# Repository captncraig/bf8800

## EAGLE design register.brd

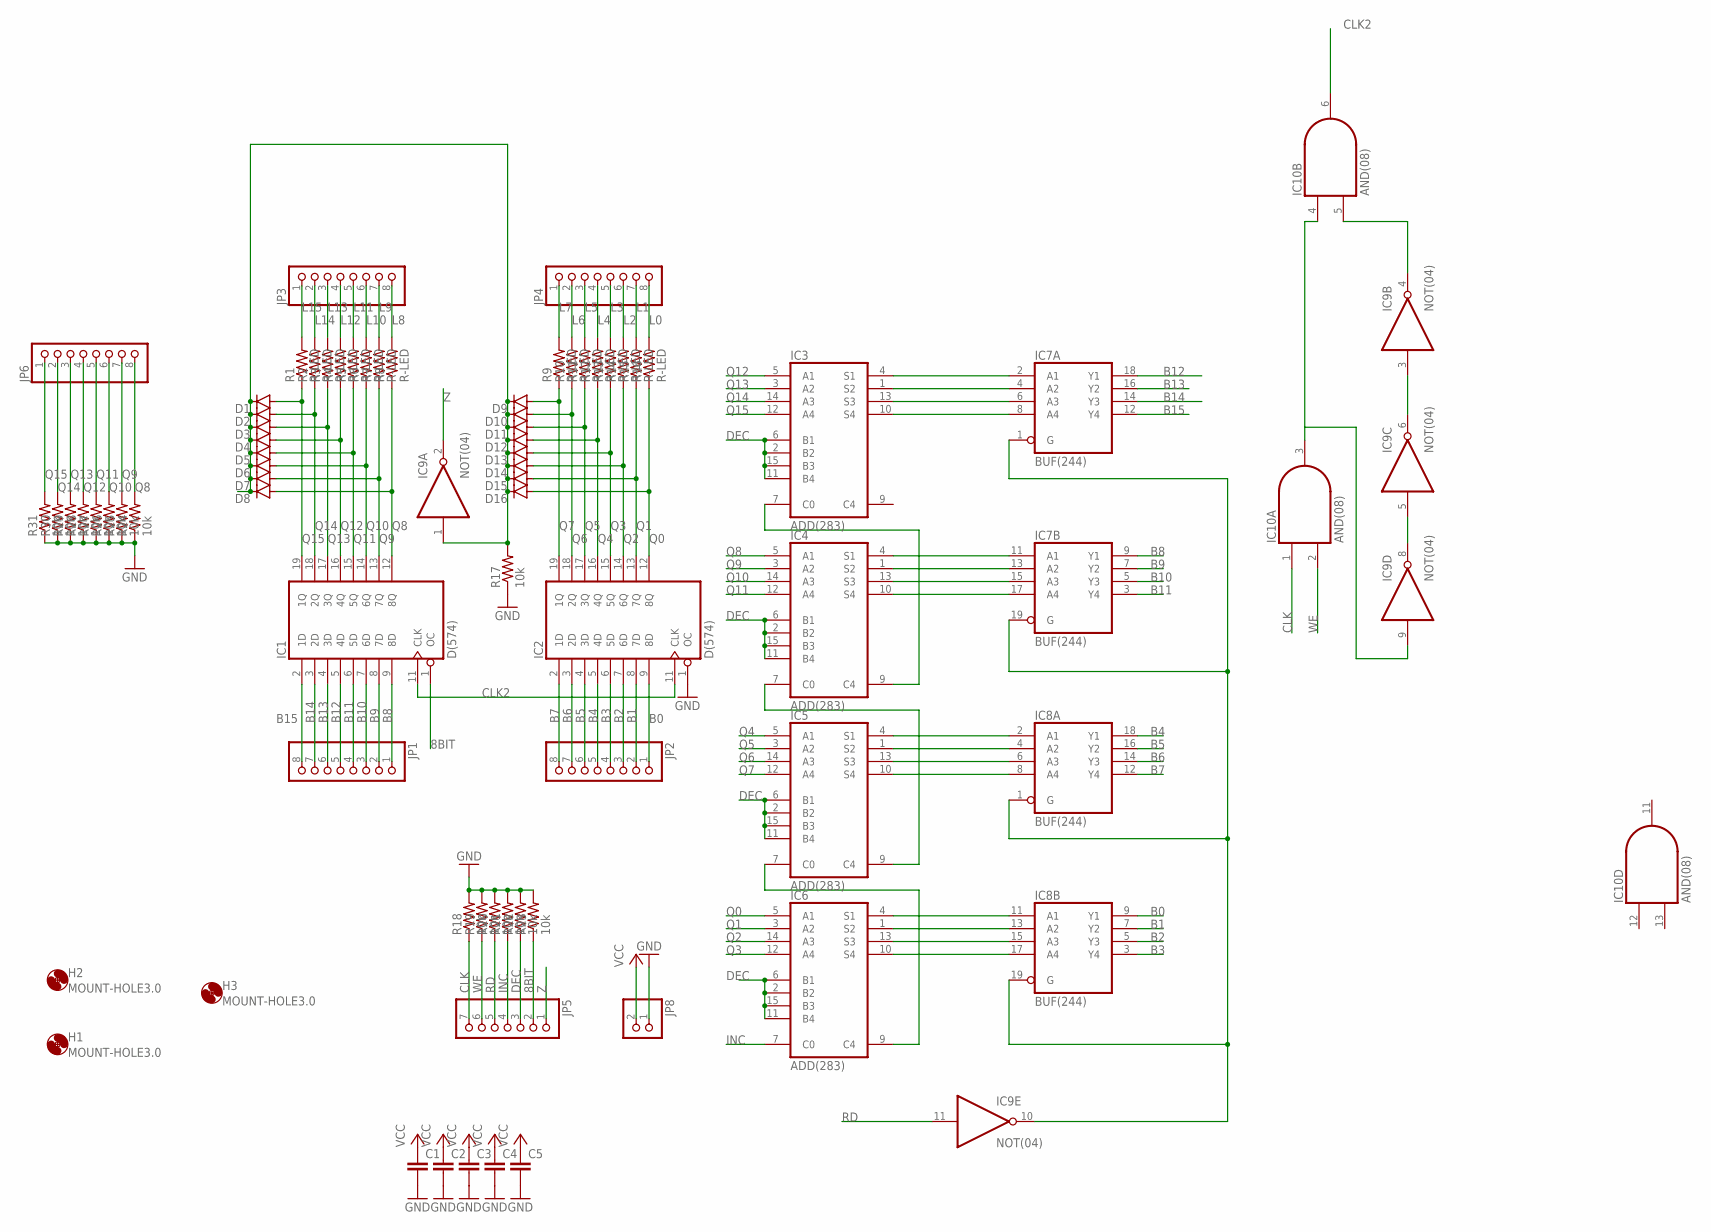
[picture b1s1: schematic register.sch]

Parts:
C1, C2, C3, C4, C5: C-Decouple; C025-025X050
D1, D2, D3, D4, D5, D6, D7, D8, D9, D10, D11, D12, D13, D14, D15, D16: DIODE-D-7.5; D-7.5
H1, H2, H3: MOUNT-HOLE3.0; 3,0
IC1, IC2: D(574); DIL20; MOUSER 595-SN74HCT574NE4
IC3, IC4, IC5, IC6: ADD(283); DIL16; MOUSER 595-CD74HCT283E
IC7, IC8: BUF(244); DIL20; MOUSER 595-SN74HCT244NE4
IC9: NOT(04); DIL14; MOUSER 595-SN74HCT04NE4
IC10: AND(08); DIL14; MOUSER 595-SN74HC08AN
JP1, JP2, JP3, JP4, JP6: PINHD-1X8; 1X08
JP5: PINHD-1X7; 1X07
JP8: PINHD-1X2; 1X02
R1, R2, R3, R4, R5, R6, R7, R8, R9, R10, R11, R12, R13, R14, R15, R16: R-LED; 0204/7
R17, R18, R19, R20, R21, R22, R23, R24, R25, R26, R27, R28, R29, R30, R31: 10k; 0204/7; MOUSER 603-MFR-12FRF5210K

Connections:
8BIT: IC1.1 (OC), JP5.2, R23.1
B0: IC2.9 (8D), IC8.9 (Y1), JP2.1
B1: IC2.8 (7D), IC8.7 (Y2), JP2.2
B2: IC2.7 (6D), IC8.5 (Y3), JP2.3
B3: IC2.6 (5D), IC8.3 (Y4), JP2.4
B4: IC2.5 (4D), IC8.18 (Y1), JP2.5
B5: IC2.4 (3D), IC8.16 (Y2), JP2.6
B6: IC2.3 (2D), IC8.14 (Y3), JP2.7
B7: IC2.2 (1D), IC8.12 (Y4), JP2.8
B8: IC1.9 (8D), IC7.9 (Y1), JP1.1
B9: IC1.8 (7D), IC7.7 (Y2), JP1.2
B10: IC1.7 (6D), IC7.5 (Y3), JP1.3
B11: IC1.6 (5D), IC7.3 (Y4), JP1.4
B12: IC1.5 (4D), IC7.18 (Y1), JP1.5
B13: IC1.4 (3D), IC7.16 (Y2), JP1.6
B14: IC1.3 (2D), IC7.14 (Y3), JP1.7
B15: IC1.2 (1D), IC7.12 (Y4), JP1.8
CLK: IC10.1 (I0), JP5.7, R18.1
CLK2: IC1.11 (CLK), IC2.11 (CLK), IC10.6 (O)
DEC: IC3.2 (B2), IC3.6 (B1), IC3.11 (B4), IC3.15 (B3), IC4.2 (B2), IC4.6 (B1), IC4.11 (B4), IC4.15 (B3), IC5.2 (B2), IC5.6 (B1), IC5.11 (B4), IC5.15 (B3), IC6.2 (B2), IC6.6 (B1), IC6.11 (B4), IC6.15 (B3), JP5.3, R22.1
GND: C1.2, C2.2, C3.2, C4.2, C5.2, IC1.10 (GND), IC2.1 (OC), IC2.10 (GND), IC3.8 (GND), IC4.8 (GND), IC5.8 (GND), IC6.8 (GND), IC7.10 (GND), IC8.10 (GND), IC9.7 (GND), IC10.7 (GND), JP8.1, R17.1, R18.2, R19.2, R20.2, R21.2, R22.2, R23.2, R24.1, R25.1, R26.1, R27.1, R28.1, R29.1, R30.1, R31.1
INC: IC6.7 (C0), JP5.4, R21.1
L0: JP4.8, R16.2
L1: JP4.7, R15.2
L2: JP4.6, R14.2
L3: JP4.5, R13.2
L4: JP4.4, R12.2
L5: JP4.3, R11.2
L6: JP4.2, R10.2
L7: JP4.1, R9.2
L8: JP3.8, R8.2
L9: JP3.7, R7.2
L10: JP3.6, R6.2
L11: JP3.5, R5.2
L12: JP3.4, R4.2
L13: JP3.3, R3.2
L14: JP3.2, R2.2
L15: JP3.1, R1.2
unnamed: IC5.7 (C0), IC6.9 (C4)
unnamed: IC9.9 (I), IC10.3 (O), IC10.4 (I0)
unnamed: D1.C, D2.C, D3.C, D4.C, D5.C, D6.C, D7.C, D8.C, D9.C, D10.C, D11.C, D12.C, D13.C, D14.C, D15.C, D16.C, IC9.1 (I), R17.2
unnamed: IC7.1 (G), IC7.19 (G), IC8.1 (G), IC8.19 (G), IC9.10 (O)
unnamed: IC9.4 (O), IC10.5 (I1)
unnamed: IC9.3 (I), IC9.6 (O)
unnamed: IC9.5 (I), IC9.8 (O)
unnamed: IC4.7 (C0), IC5.9 (C4)
unnamed: IC3.7 (C0), IC4.9 (C4)
unnamed: IC3.4 (S1), IC7.2 (A1)
unnamed: IC3.1 (S2), IC7.4 (A2)
unnamed: IC3.13 (S3), IC7.6 (A3)
unnamed: IC3.10 (S4), IC7.8 (A4)
unnamed: IC4.4 (S1), IC7.11 (A1)
unnamed: IC4.1 (S2), IC7.13 (A2)
unnamed: IC4.13 (S3), IC7.15 (A3)
unnamed: IC4.10 (S4), IC7.17 (A4)
unnamed: IC5.4 (S1), IC8.2 (A1)
unnamed: IC5.1 (S2), IC8.4 (A2)
unnamed: IC5.13 (S3), IC8.6 (A3)
unnamed: IC5.10 (S4), IC8.8 (A4)
unnamed: IC6.4 (S1), IC8.11 (A1)
unnamed: IC6.1 (S2), IC8.13 (A2)
unnamed: IC6.13 (S3), IC8.15 (A3)
unnamed: IC6.10 (S4), IC8.17 (A4)
Q0: D16.A, IC2.12 (8Q), IC6.5 (A1), R16.1
Q1: D15.A, IC2.13 (7Q), IC6.3 (A2), R15.1
Q2: D14.A, IC2.14 (6Q), IC6.14 (A3), R14.1
Q3: D13.A, IC2.15 (5Q), IC6.12 (A4), R13.1
Q4: D12.A, IC2.16 (4Q), IC5.5 (A1), R12.1
Q5: D11.A, IC2.17 (3Q), IC5.3 (A2), R11.1
Q6: D10.A, IC2.18 (2Q), IC5.14 (A3), R10.1
Q7: D9.A, IC2.19 (1Q), IC5.12 (A4), R9.1
Q8: D8.A, IC1.12 (8Q), IC4.5 (A1), JP6.8, R8.1, R24.2
Q9: D7.A, IC1.13 (7Q), IC4.3 (A2), JP6.7, R7.1, R25.2
Q10: D6.A, IC1.14 (6Q), IC4.14 (A3), JP6.6, R6.1, R26.2
Q11: D5.A, IC1.15 (5Q), IC4.12 (A4), JP6.5, R5.1, R27.2
Q12: D4.A, IC1.16 (4Q), IC3.5 (A1), JP6.4, R4.1, R28.2
Q13: D3.A, IC1.17 (3Q), IC3.3 (A2), JP6.3, R3.1, R29.2
Q14: D2.A, IC1.18 (2Q), IC3.14 (A3), JP6.2, R2.1, R30.2
Q15: D1.A, IC1.19 (1Q), IC3.12 (A4), JP6.1, R1.1, R31.2
RD: IC9.11 (I), JP5.5, R20.1
VCC: C1.1, C2.1, C3.1, C4.1, C5.1, IC1.20 (VCC), IC2.20 (VCC), IC3.16 (VCC), IC4.16 (VCC), IC5.16 (VCC), IC6.16 (VCC), IC7.20 (VCC), IC8.20 (VCC), IC9.14 (VCC), IC10.14 (VCC), JP8.2
WE: IC10.2 (I1), JP5.6, R19.1
Z: IC9.2 (O), JP5.1

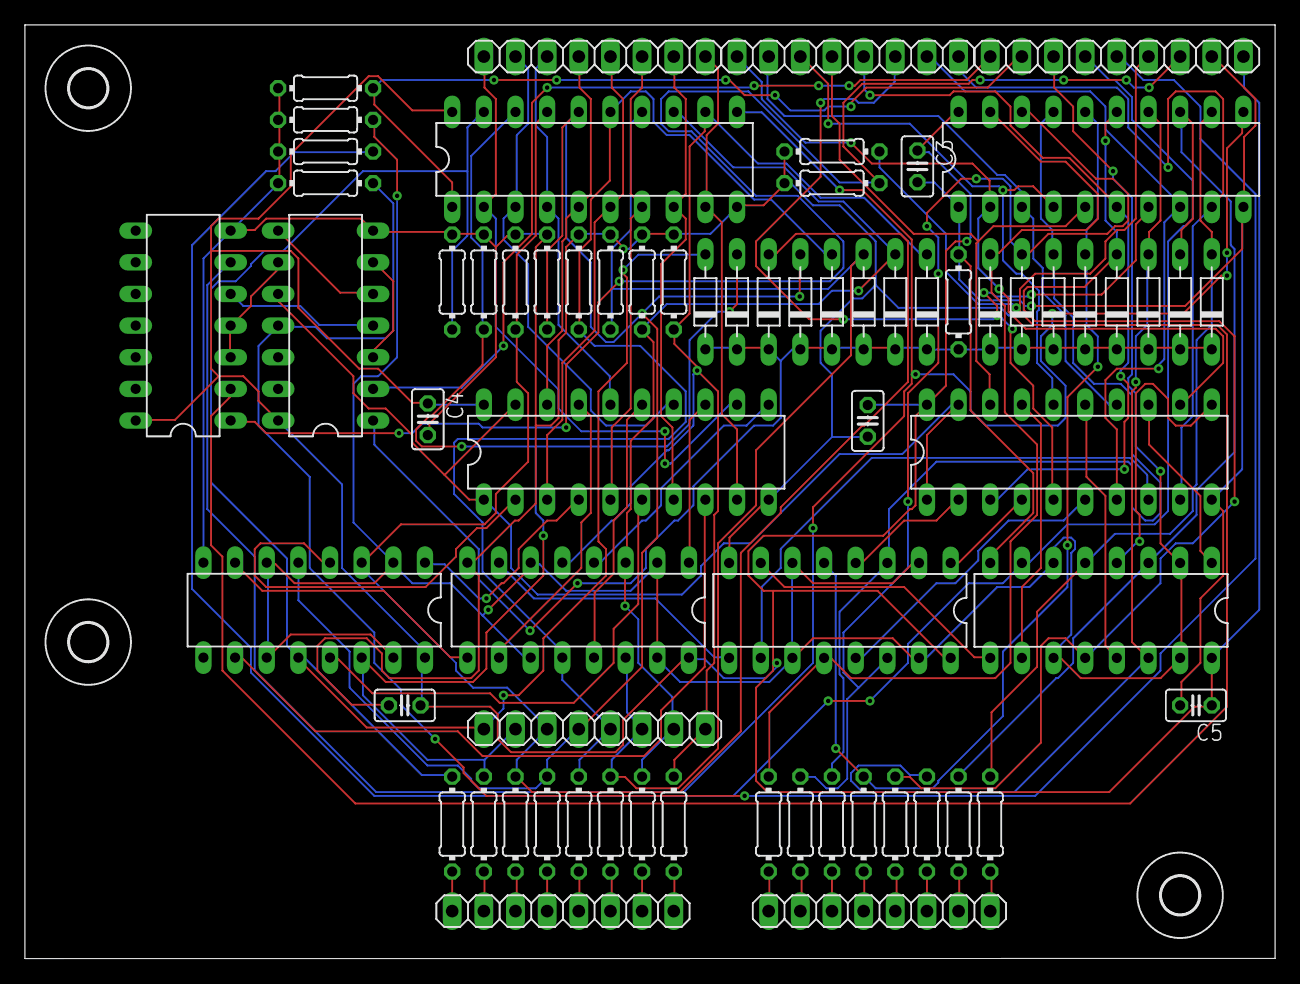
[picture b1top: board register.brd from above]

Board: 2 copper layers, 100.3 x 74.9 mm, 72 parts (0 on the bottom side), 83 nets.

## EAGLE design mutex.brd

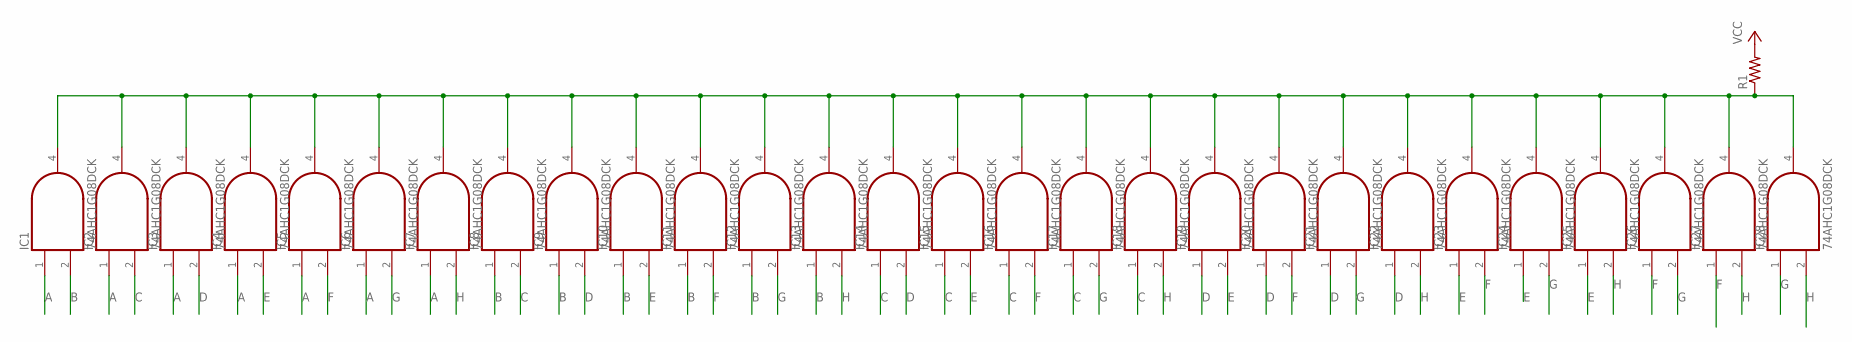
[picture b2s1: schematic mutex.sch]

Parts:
IC1, IC2, IC3, IC4, IC5, IC6, IC7, IC8, IC9, IC10, IC11, IC12, IC13, IC14, IC15, IC16, IC17, IC18, IC19, IC20, IC21, IC22, IC23, IC24, IC25, IC26, IC27, IC28: 74AHC1G08DCK; SC70-5
R1: R-US_0207/7; 0207/7

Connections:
A: IC1.1 (I0), IC2.1 (I0), IC3.1 (I0), IC4.1 (I0), IC5.1 (I0), IC6.1 (I0), IC7.1 (I0)
B: IC1.2 (I1), IC8.1 (I0), IC9.1 (I0), IC10.1 (I0), IC11.1 (I0), IC12.1 (I0), IC13.1 (I0)
C: IC2.2 (I1), IC8.2 (I1), IC14.1 (I0), IC15.1 (I0), IC16.1 (I0), IC17.1 (I0), IC18.1 (I0)
D: IC3.2 (I1), IC9.2 (I1), IC14.2 (I1), IC19.1 (I0), IC20.1 (I0), IC21.1 (I0), IC22.1 (I0)
E: IC4.2 (I1), IC10.2 (I1), IC15.2 (I1), IC19.2 (I1), IC23.1 (I0), IC24.1 (I0), IC25.1 (I0)
F: IC5.2 (I1), IC11.2 (I1), IC16.2 (I1), IC20.2 (I1), IC23.2 (I1), IC26.1 (I0), IC27.1 (I0)
G: IC6.2 (I1), IC12.2 (I1), IC17.2 (I1), IC21.2 (I1), IC24.2 (I1), IC26.2 (I1), IC28.1 (I0)
GND: IC1.3 (GND), IC2.3 (GND), IC3.3 (GND), IC4.3 (GND), IC5.3 (GND), IC6.3 (GND), IC7.3 (GND), IC8.3 (GND), IC9.3 (GND), IC10.3 (GND), IC11.3 (GND), IC12.3 (GND), IC13.3 (GND), IC14.3 (GND), IC15.3 (GND), IC16.3 (GND), IC17.3 (GND), IC18.3 (GND), IC19.3 (GND), IC20.3 (GND), IC21.3 (GND), IC22.3 (GND), IC23.3 (GND), IC24.3 (GND), IC25.3 (GND), IC26.3 (GND), IC27.3 (GND), IC28.3 (GND)
H: IC7.2 (I1), IC13.2 (I1), IC18.2 (I1), IC22.2 (I1), IC25.2 (I1), IC27.2 (I1), IC28.2 (I1)
unnamed: IC1.4 (O), IC2.4 (O), IC3.4 (O), IC4.4 (O), IC5.4 (O), IC6.4 (O), IC7.4 (O), IC8.4 (O), IC9.4 (O), IC10.4 (O), IC11.4 (O), IC12.4 (O), IC13.4 (O), IC14.4 (O), IC15.4 (O), IC16.4 (O), IC17.4 (O), IC18.4 (O), IC19.4 (O), IC20.4 (O), IC21.4 (O), IC22.4 (O), IC23.4 (O), IC24.4 (O), IC25.4 (O), IC26.4 (O), IC27.4 (O), IC28.4 (O), R1.1
VCC: IC1.5 (VCC), IC2.5 (VCC), IC3.5 (VCC), IC4.5 (VCC), IC5.5 (VCC), IC6.5 (VCC), IC7.5 (VCC), IC8.5 (VCC), IC9.5 (VCC), IC10.5 (VCC), IC11.5 (VCC), IC12.5 (VCC), IC13.5 (VCC), IC14.5 (VCC), IC15.5 (VCC), IC16.5 (VCC), IC17.5 (VCC), IC18.5 (VCC), IC19.5 (VCC), IC20.5 (VCC), IC21.5 (VCC), IC22.5 (VCC), IC23.5 (VCC), IC24.5 (VCC), IC25.5 (VCC), IC26.5 (VCC), IC27.5 (VCC), IC28.5 (VCC), R1.2

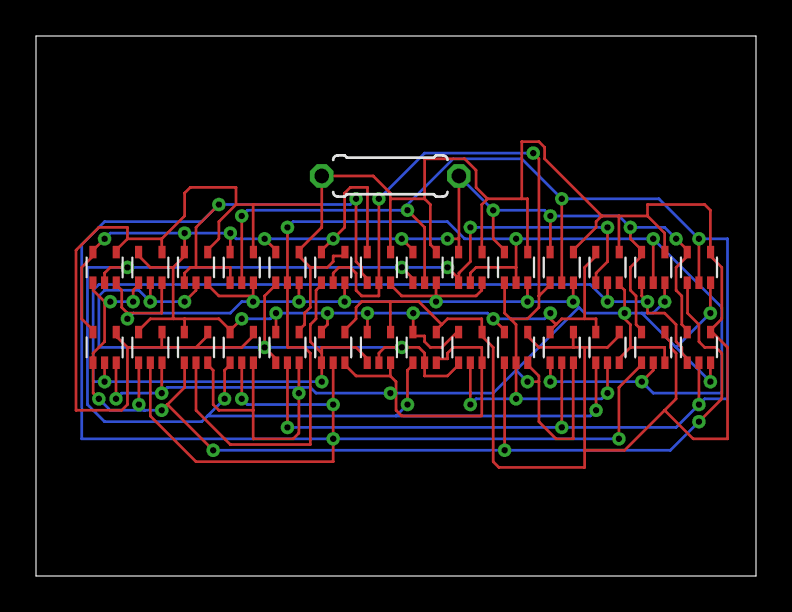
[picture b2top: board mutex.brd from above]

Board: 2 copper layers, 40.0 x 30.0 mm, 29 parts (0 on the bottom side), 11 nets.

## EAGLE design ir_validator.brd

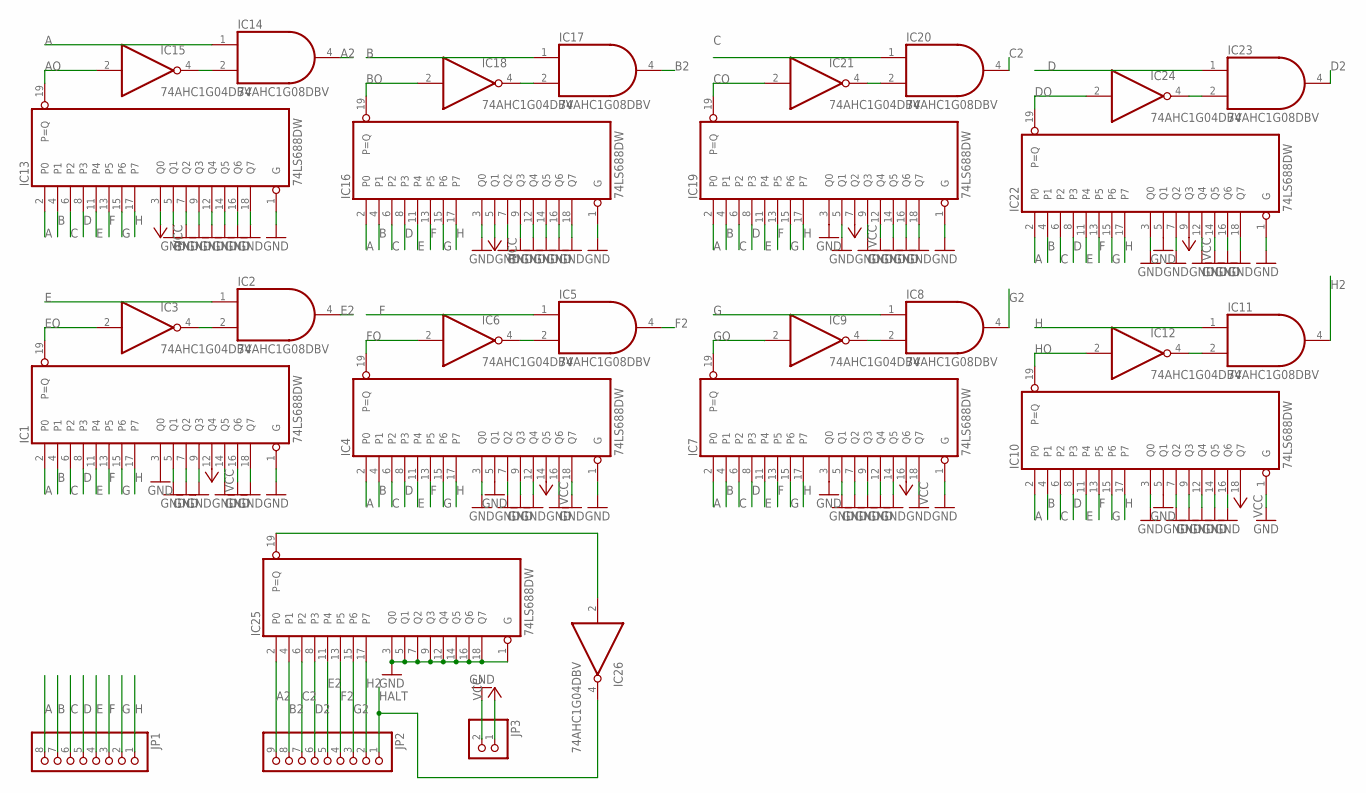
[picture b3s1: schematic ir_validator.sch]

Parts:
IC1, IC4, IC7, IC10, IC13, IC16, IC19, IC22, IC25: 74LS688DW; SO20W
IC2, IC5, IC8, IC11, IC14, IC17, IC20, IC23: 74AHC1G08DBV; SOT23-5
IC3, IC6, IC9, IC12, IC15, IC18, IC21, IC24, IC26: 74AHC1G04DBV; SOT23-5
JP1: PINHD-1X8; 1X08
JP2: PINHD-1X9; 1X09
JP3: PINHD-1X2; 1X02

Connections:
A: IC1.2 (P0), IC4.2 (P0), IC7.2 (P0), IC10.2 (P0), IC13.2 (P0), IC14.1 (I0), IC16.2 (P0), IC19.2 (P0), IC22.2 (P0), JP1.8
A2: IC14.4 (O), IC25.2 (P0), JP2.9
AO: IC13.19 (P=Q), IC15.2 (I)
B: IC1.4 (P1), IC4.4 (P1), IC7.4 (P1), IC10.4 (P1), IC13.4 (P1), IC16.4 (P1), IC17.1 (I0), IC19.4 (P1), IC22.4 (P1), JP1.7
B2: IC17.4 (O), IC25.4 (P1), JP2.8
BO: IC16.19 (P=Q), IC18.2 (I)
C: IC1.6 (P2), IC4.6 (P2), IC7.6 (P2), IC10.6 (P2), IC13.6 (P2), IC16.6 (P2), IC19.6 (P2), IC20.1 (I0), IC22.6 (P2), JP1.6
C2: IC20.4 (O), IC25.6 (P2), JP2.7
CO: IC19.19 (P=Q), IC21.2 (I)
D: IC1.8 (P3), IC4.8 (P3), IC7.8 (P3), IC10.8 (P3), IC13.8 (P3), IC16.8 (P3), IC19.8 (P3), IC22.8 (P3), IC23.1 (I0), JP1.5
D2: IC23.4 (O), IC25.8 (P3), JP2.6
DO: IC22.19 (P=Q), IC24.2 (I)
E: IC1.11 (P4), IC2.1 (I0), IC4.11 (P4), IC7.11 (P4), IC10.11 (P4), IC13.11 (P4), IC16.11 (P4), IC19.11 (P4), IC22.11 (P4), JP1.4
E2: IC2.4 (O), IC25.11 (P4), JP2.5
EO: IC1.19 (P=Q), IC3.2 (I)
F: IC1.13 (P5), IC4.13 (P5), IC5.1 (I0), IC7.13 (P5), IC10.13 (P5), IC13.13 (P5), IC16.13 (P5), IC19.13 (P5), IC22.13 (P5), JP1.3
F2: IC5.4 (O), IC25.13 (P5), JP2.4
FO: IC4.19 (P=Q), IC6.2 (I)
G: IC1.15 (P6), IC4.15 (P6), IC7.15 (P6), IC8.1 (I0), IC10.15 (P6), IC13.15 (P6), IC16.15 (P6), IC19.15 (P6), IC22.15 (P6), JP1.2
G2: IC8.4 (O), IC25.15 (P6), JP2.3
GND: IC1.1 (G), IC1.3 (Q0), IC1.5 (Q1), IC1.7 (Q2), IC1.9 (Q3), IC1.10 (GND), IC1.14 (Q5), IC1.16 (Q6), IC1.18 (Q7), IC2.3 (GND), IC3.3 (GND), IC4.1 (G), IC4.3 (Q0), IC4.5 (Q1), IC4.7 (Q2), IC4.9 (Q3), IC4.10 (GND), IC4.12 (Q4), IC4.16 (Q6), IC4.18 (Q7), IC5.3 (GND), IC6.3 (GND), IC7.1 (G), IC7.3 (Q0), IC7.5 (Q1), IC7.7 (Q2), IC7.9 (Q3), IC7.10 (GND), IC7.12 (Q4), IC7.14 (Q5), IC7.18 (Q7), IC8.3 (GND), IC9.3 (GND), IC10.1 (G), IC10.3 (Q0), IC10.5 (Q1), IC10.7 (Q2), IC10.9 (Q3), IC10.10 (GND), IC10.12 (Q4), IC10.14 (Q5), IC10.16 (Q6), IC11.3 (GND), IC12.3 (GND), IC13.1 (G), IC13.5 (Q1), IC13.7 (Q2), IC13.9 (Q3), IC13.10 (GND), IC13.12 (Q4), IC13.14 (Q5), IC13.16 (Q6), IC13.18 (Q7), IC14.3 (GND), IC15.3 (GND), IC16.1 (G), IC16.3 (Q0), IC16.7 (Q2), IC16.9 (Q3), IC16.10 (GND), IC16.12 (Q4), IC16.14 (Q5), IC16.16 (Q6), IC16.18 (Q7), IC17.3 (GND), IC18.3 (GND), IC19.1 (G), IC19.3 (Q0), IC19.5 (Q1), IC19.9 (Q3), IC19.10 (GND), IC19.12 (Q4), IC19.14 (Q5), IC19.16 (Q6), IC19.18 (Q7), IC20.3 (GND), IC21.3 (GND), IC22.1 (G), IC22.3 (Q0), IC22.5 (Q1), IC22.7 (Q2), IC22.10 (GND), IC22.12 (Q4), IC22.14 (Q5), IC22.16 (Q6), IC22.18 (Q7), IC23.3 (GND), IC24.3 (GND), IC25.1 (G), IC25.3 (Q0), IC25.5 (Q1), IC25.7 (Q2), IC25.9 (Q3), IC25.10 (GND), IC25.12 (Q4), IC25.14 (Q5), IC25.16 (Q6), IC25.18 (Q7), IC26.3 (GND), JP3.2
GO: IC7.19 (P=Q), IC9.2 (I)
H: IC1.17 (P7), IC4.17 (P7), IC7.17 (P7), IC10.17 (P7), IC11.1 (I0), IC13.17 (P7), IC16.17 (P7), IC19.17 (P7), IC22.17 (P7), JP1.1
H2: IC11.4 (O), IC25.17 (P7), JP2.2
HALT: IC26.4 (O), JP2.1
HO: IC10.19 (P=Q), IC12.2 (I)
unnamed: IC25.19 (P=Q), IC26.2 (I)
unnamed: IC2.2 (I1), IC3.4 (O)
unnamed: IC5.2 (I1), IC6.4 (O)
unnamed: IC8.2 (I1), IC9.4 (O)
unnamed: IC11.2 (I1), IC12.4 (O)
unnamed: IC14.2 (I1), IC15.4 (O)
unnamed: IC17.2 (I1), IC18.4 (O)
unnamed: IC20.2 (I1), IC21.4 (O)
unnamed: IC23.2 (I1), IC24.4 (O)
VCC: IC1.12 (Q4), IC1.20 (VCC), IC2.5 (VCC), IC3.5 (VCC), IC4.14 (Q5), IC4.20 (VCC), IC5.5 (VCC), IC6.5 (VCC), IC7.16 (Q6), IC7.20 (VCC), IC8.5 (VCC), IC9.5 (VCC), IC10.18 (Q7), IC10.20 (VCC), IC11.5 (VCC), IC12.5 (VCC), IC13.3 (Q0), IC13.20 (VCC), IC14.5 (VCC), IC15.5 (VCC), IC16.5 (Q1), IC16.20 (VCC), IC17.5 (VCC), IC18.5 (VCC), IC19.7 (Q2), IC19.20 (VCC), IC20.5 (VCC), IC21.5 (VCC), IC22.9 (Q3), IC22.20 (VCC), IC23.5 (VCC), IC24.5 (VCC), IC25.20 (VCC), IC26.5 (VCC), JP3.1

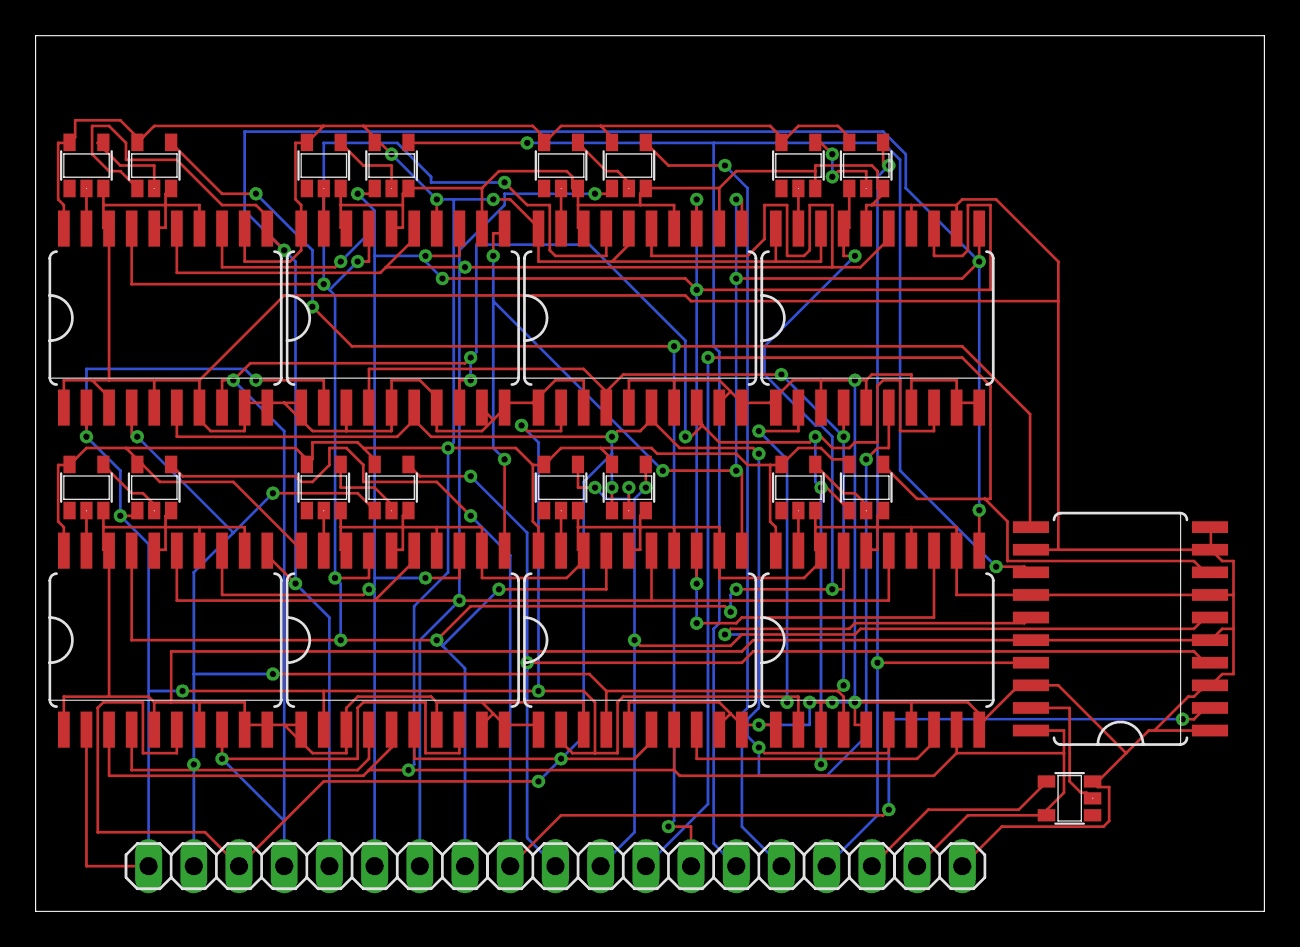
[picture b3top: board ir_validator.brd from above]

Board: 2 copper layers, 69.0 x 49.2 mm, 29 parts (0 on the bottom side), 36 nets.

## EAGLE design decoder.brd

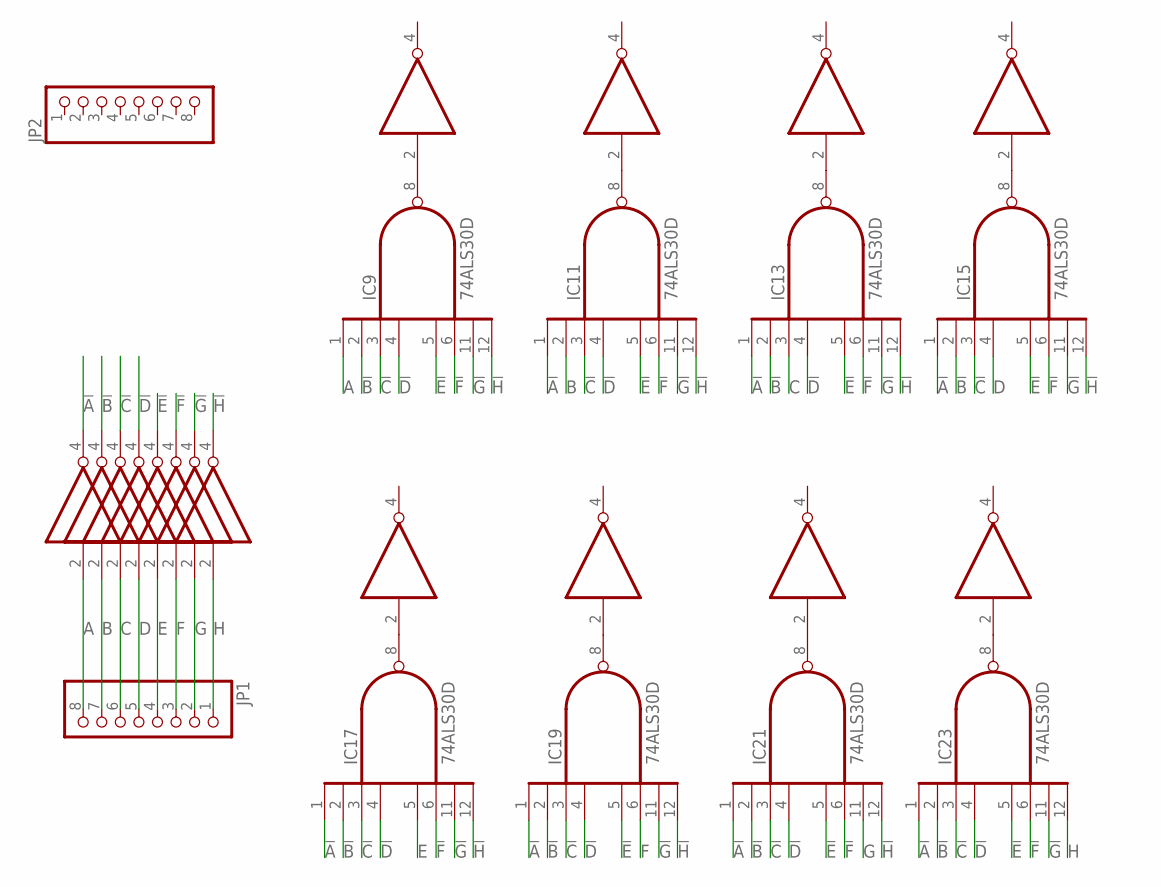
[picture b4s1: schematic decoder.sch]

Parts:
IC1, IC2, IC3, IC4, IC5, IC6, IC7, IC8, IC10, IC12, IC14, IC16, IC18, IC20, IC22, IC24: 74AUC1G04DBV; SOT23-5
IC9, IC11, IC13, IC15, IC17, IC19, IC21, IC23: 74ALS30D; SO14
JP1, JP2: PINHD-1X8; 1X08

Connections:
!A: IC1.4 (O), IC11.1 (I0), IC13.1 (I0), IC15.1 (I0), IC17.1 (I0), IC19.1 (I0), IC21.1 (I0), IC23.1 (I0)
!B: IC2.4 (O), IC9.2 (I1), IC13.2 (I1), IC15.2 (I1), IC17.2 (I1), IC19.2 (I1), IC21.2 (I1), IC23.2 (I1)
!C: IC3.4 (O), IC9.3 (I2), IC11.3 (I2), IC15.3 (I2), IC17.3 (I2), IC19.3 (I2), IC21.3 (I2), IC23.3 (I2)
!D: IC4.4 (O), IC9.4 (I3), IC11.4 (I3), IC13.4 (I3), IC17.4 (I3), IC19.4 (I3), IC21.4 (I3), IC23.4 (I3)
!E: IC5.4 (O), IC9.5 (I4), IC11.5 (I4), IC13.5 (I4), IC15.5 (I4), IC19.5 (I4), IC21.5 (I4), IC23.5 (I4)
!F: IC6.4 (O), IC9.6 (I5), IC11.6 (I5), IC13.6 (I5), IC15.6 (I5), IC17.6 (I5), IC21.6 (I5), IC23.6 (I5)
!G: IC7.4 (O), IC9.11 (I6), IC11.11 (I6), IC13.11 (I6), IC15.11 (I6), IC17.11 (I6), IC19.11 (I6), IC23.11 (I6)
!H: IC8.4 (O), IC9.12 (I7), IC11.12 (I7), IC13.12 (I7), IC15.12 (I7), IC17.12 (I7), IC19.12 (I7), IC21.12 (I7)
A: IC1.2 (I), IC9.1 (I0), JP1.8
B: IC2.2 (I), IC11.2 (I1), JP1.7
C: IC3.2 (I), IC13.3 (I2), JP1.6
D: IC4.2 (I), IC15.4 (I3), JP1.5
E: IC5.2 (I), IC17.5 (I4), JP1.4
F: IC6.2 (I), IC19.6 (I5), JP1.3
G: IC7.2 (I), IC21.11 (I6), JP1.2
GND: IC1.3 (GND), IC2.3 (GND), IC3.3 (GND), IC4.3 (GND), IC5.3 (GND), IC6.3 (GND), IC7.3 (GND), IC8.3 (GND), IC9.7 (GND), IC10.3 (GND), IC11.7 (GND), IC12.3 (GND), IC13.7 (GND), IC14.3 (GND), IC15.7 (GND), IC16.3 (GND), IC17.7 (GND), IC18.3 (GND), IC19.7 (GND), IC20.3 (GND), IC21.7 (GND), IC22.3 (GND), IC23.7 (GND), IC24.3 (GND)
H: IC8.2 (I), IC23.12 (I7), JP1.1
unnamed: IC9.8 (O), IC10.2 (I)
unnamed: IC11.8 (O), IC12.2 (I)
unnamed: IC13.8 (O), IC14.2 (I)
unnamed: IC15.8 (O), IC16.2 (I)
unnamed: IC17.8 (O), IC18.2 (I)
unnamed: IC19.8 (O), IC20.2 (I)
unnamed: IC21.8 (O), IC22.2 (I)
unnamed: IC23.8 (O), IC24.2 (I)
VCC: IC1.5 (VCC), IC2.5 (VCC), IC3.5 (VCC), IC4.5 (VCC), IC5.5 (VCC), IC6.5 (VCC), IC7.5 (VCC), IC8.5 (VCC), IC9.14 (VCC), IC10.5 (VCC), IC11.14 (VCC), IC12.5 (VCC), IC13.14 (VCC), IC14.5 (VCC), IC15.14 (VCC), IC16.5 (VCC), IC17.14 (VCC), IC18.5 (VCC), IC19.14 (VCC), IC20.5 (VCC), IC21.14 (VCC), IC22.5 (VCC), IC23.14 (VCC), IC24.5 (VCC)

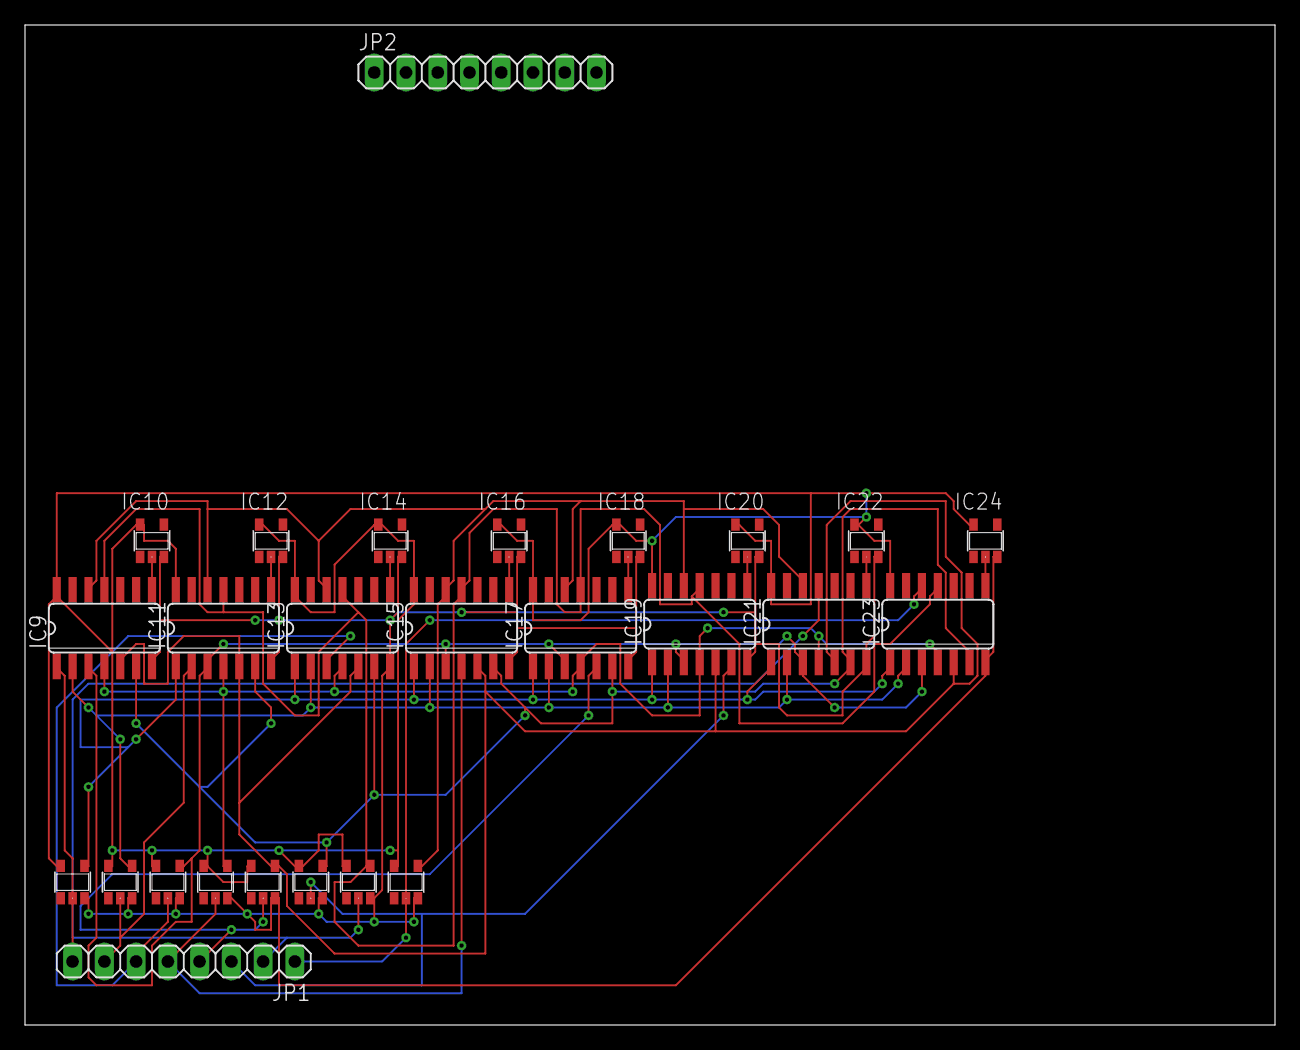
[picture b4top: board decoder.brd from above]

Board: 2 copper layers, 100.0 x 80.0 mm, 26 parts (0 on the bottom side), 26 nets.

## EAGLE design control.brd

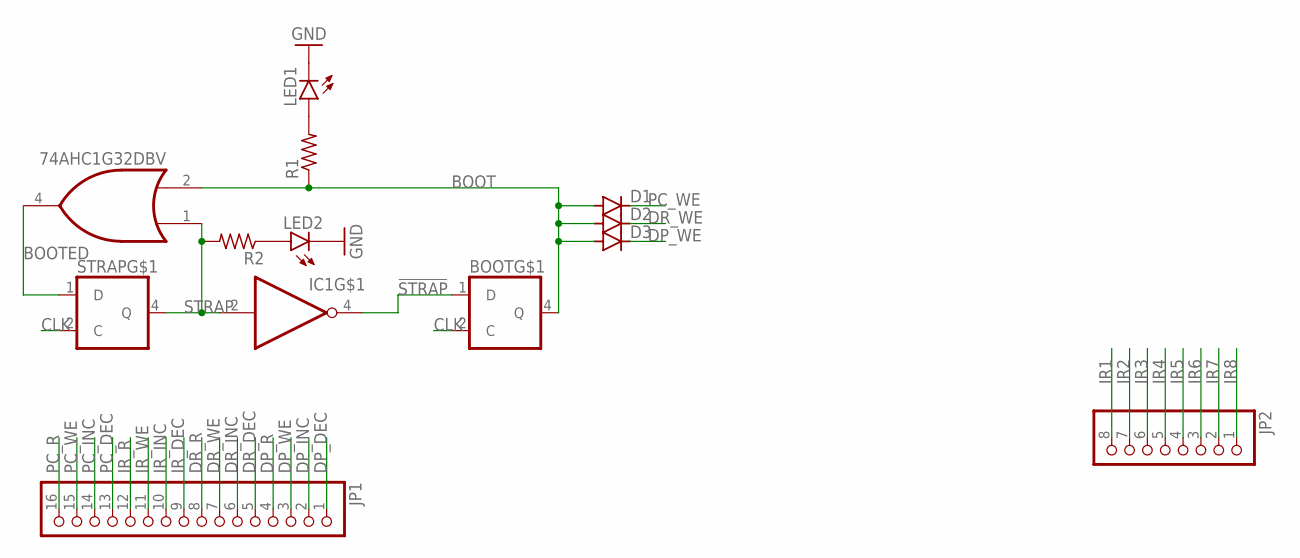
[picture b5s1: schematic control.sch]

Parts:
BOOT: 74LVC1G79DBV; SOT23-5
D1, D2, D3: DIODE-SOD323-W; SOD323-W
IC1: 74AUC1G06DBV; SOT23-5
IC2: 74AHC1G32DBV; SOT23-5
JP1: PINHD-1X16; 1X16
JP2: PINHD-1X8; 1X08
LED1, LED2: LEDCHIP-LED0603; CHIP-LED0603
R1, R2: R-US_R0603; R0603
STRAP: 74LVC1G79DBV; SOT23-5

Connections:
!STRAP: BOOT.1 (D), IC1.4 (O)
BOOT: BOOT.4 (Q), D1.A, D2.A, D3.A, IC2.2 (I1), R1.1
BOOTED: IC2.4 (O), STRAP.1 (D)
CLK: BOOT.2 (C), STRAP.2 (C)
DP_DEC: JP1.1
DP_INC: JP1.2
DP_R: JP1.4
DP_WE: D3.C, JP1.3
DR_DEC: JP1.5
DR_INC: JP1.6
DR_R: JP1.8
DR_WE: D2.C, JP1.7
GND: BOOT.3 (GND), IC1.3 (GND), IC2.3 (GND), LED1.C, LED2.C, STRAP.3 (GND)
IR1: JP2.8
IR2: JP2.7
IR3: JP2.6
IR4: JP2.5
IR5: JP2.4
IR6: JP2.3
IR7: JP2.2
IR8: JP2.1
IR_DEC: JP1.9
IR_INC: JP1.10
IR_R: JP1.12
IR_WE: JP1.11
unnamed: LED1.A, R1.2
unnamed: LED2.A, R2.1
PC_DEC: JP1.13
PC_INC: JP1.14
PC_R: JP1.16
PC_WE: D1.C, JP1.15
STRAP: IC1.2 (I), IC2.1 (I0), R2.2, STRAP.4 (Q)
VCC: BOOT.5 (VCC), IC1.5 (VCC), IC2.5 (VCC), STRAP.5 (VCC)

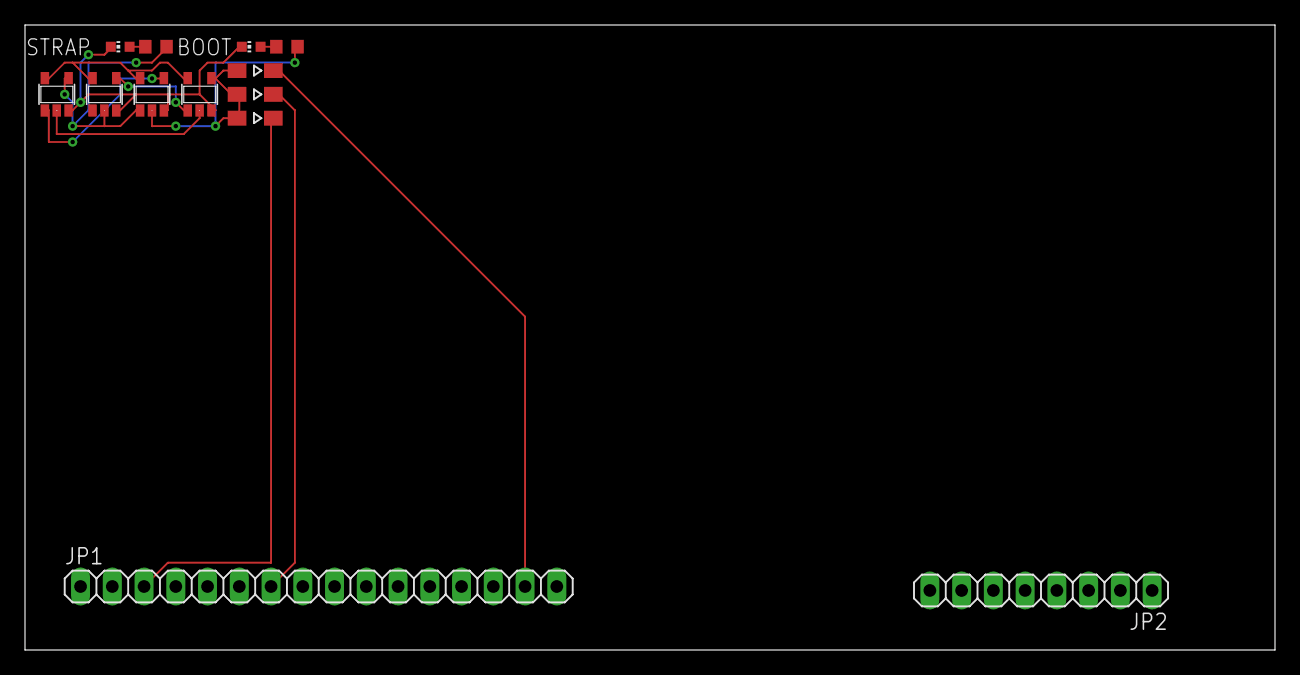
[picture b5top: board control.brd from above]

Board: 2 copper layers, 100.0 x 50.0 mm, 13 parts (0 on the bottom side), 12 nets.

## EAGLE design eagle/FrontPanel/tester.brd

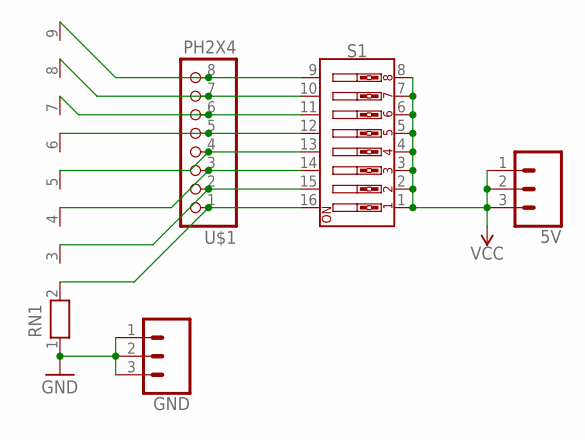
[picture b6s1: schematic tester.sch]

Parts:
5V: CONN_03; 1X03
GND: CONN_03; 1X03
RN1: RN08; RN-9
S1: DIP-08-PTH; DIPSWITCH-08
U$1: PH2X4; 2X04

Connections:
GND: GND.1, GND.2, GND.3, RN1.1
unnamed: RN1.2, S1.16, U$1.1
unnamed: RN1.3, S1.15, U$1.2
unnamed: RN1.4, S1.14, U$1.3
unnamed: RN1.5, S1.13, U$1.4
unnamed: RN1.6, S1.12, U$1.5
unnamed: RN1.7, S1.11, U$1.6
unnamed: RN1.8, S1.10, U$1.7
unnamed: RN1.9, S1.9, U$1.8
VCC: 5V.1, 5V.2, 5V.3, S1.1, S1.2, S1.3, S1.4, S1.5, S1.6, S1.7, S1.8

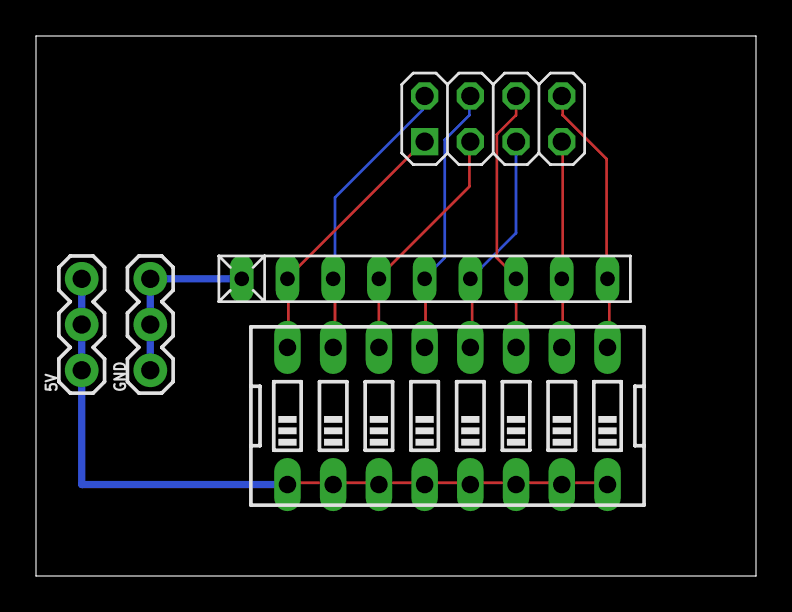
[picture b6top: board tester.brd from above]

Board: 2 copper layers, 40.0 x 30.0 mm, 5 parts (0 on the bottom side), 10 nets.

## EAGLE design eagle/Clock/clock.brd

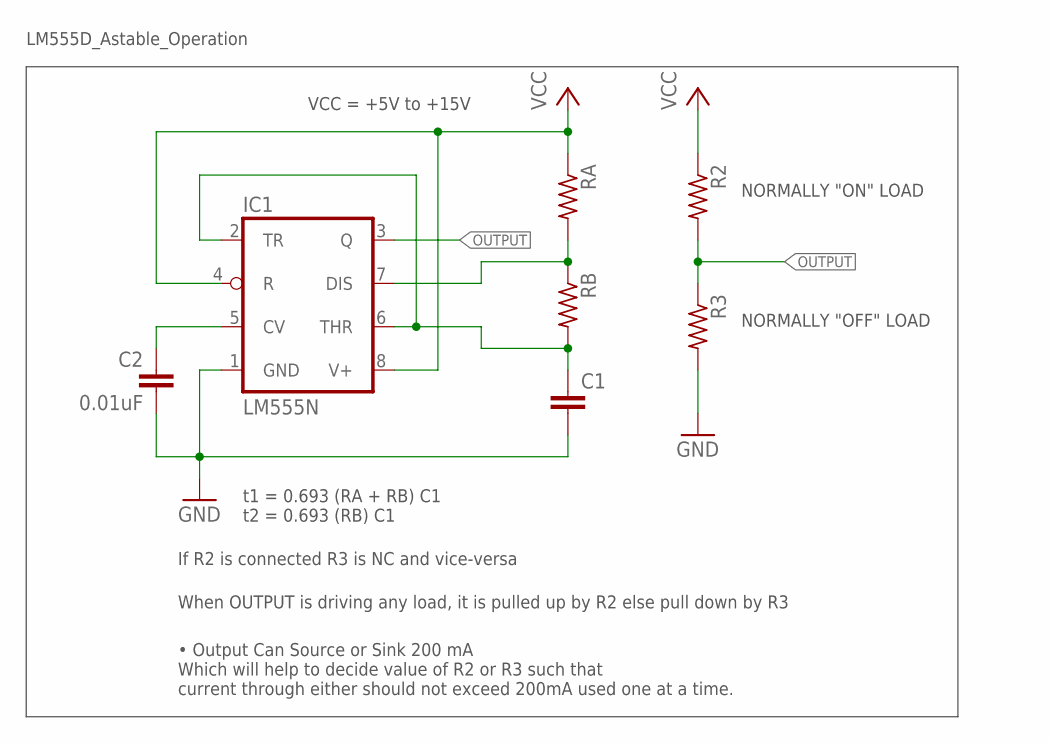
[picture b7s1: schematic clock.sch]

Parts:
C1: C-EU025-025X050; C025-025X050
C2: 0.01uF; C025-025X050
IC1: LM555N; DIL08
R2, R3: R-US_R0805; R0805
RA: R-US_R0805; R0805
RB: R-US_R0805; R0805

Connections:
GND: C1.2, C2.2, IC1.1 (GND), R3.2
unnamed: C1.1, IC1.2 (TR), IC1.6 (THR), RB.2
unnamed: IC1.7 (DIS), RA.2, RB.1
unnamed: C2.1, IC1.5 (CV)
OUTPUT: IC1.3 (Q), R2.2, R3.1
VCC: IC1.4 (R), IC1.8 (V+), R2.1, RA.1

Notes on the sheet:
NORMALLY "ON" LOAD
NORMALLY "OFF" LOAD
• Output Can Source or Sink 200 mA Which will help to decide value of R2 or R3 such that current through either should not exceed 200mA used one at a time.
When OUTPUT is driving any load, it is pulled up by R2 else pull down by R3
If R2 is connected R3 is NC and vice-versa
LM555D_Astable_Operation
t1 = 0.693 (RA + RB) C1 t2 = 0.693 (RB) C1
VCC = +5V to +15V

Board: 2 copper layers, 7 parts (0 on the bottom side), 6 nets, no tracks yet.

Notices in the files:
parts and their libraries:
SparkFun-Hardware: Licensing: Creative Commons ShareAlike 4.0 International - https://creativecommons.org/licenses/by-sa/4.0
